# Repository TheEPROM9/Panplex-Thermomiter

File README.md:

# Panplex-Thermomiter
Website Overview: https://www.theeprom9.co.uk/electronics/projects-such/panplex-thermometer
Here be the PCB files & code I developed for this project.

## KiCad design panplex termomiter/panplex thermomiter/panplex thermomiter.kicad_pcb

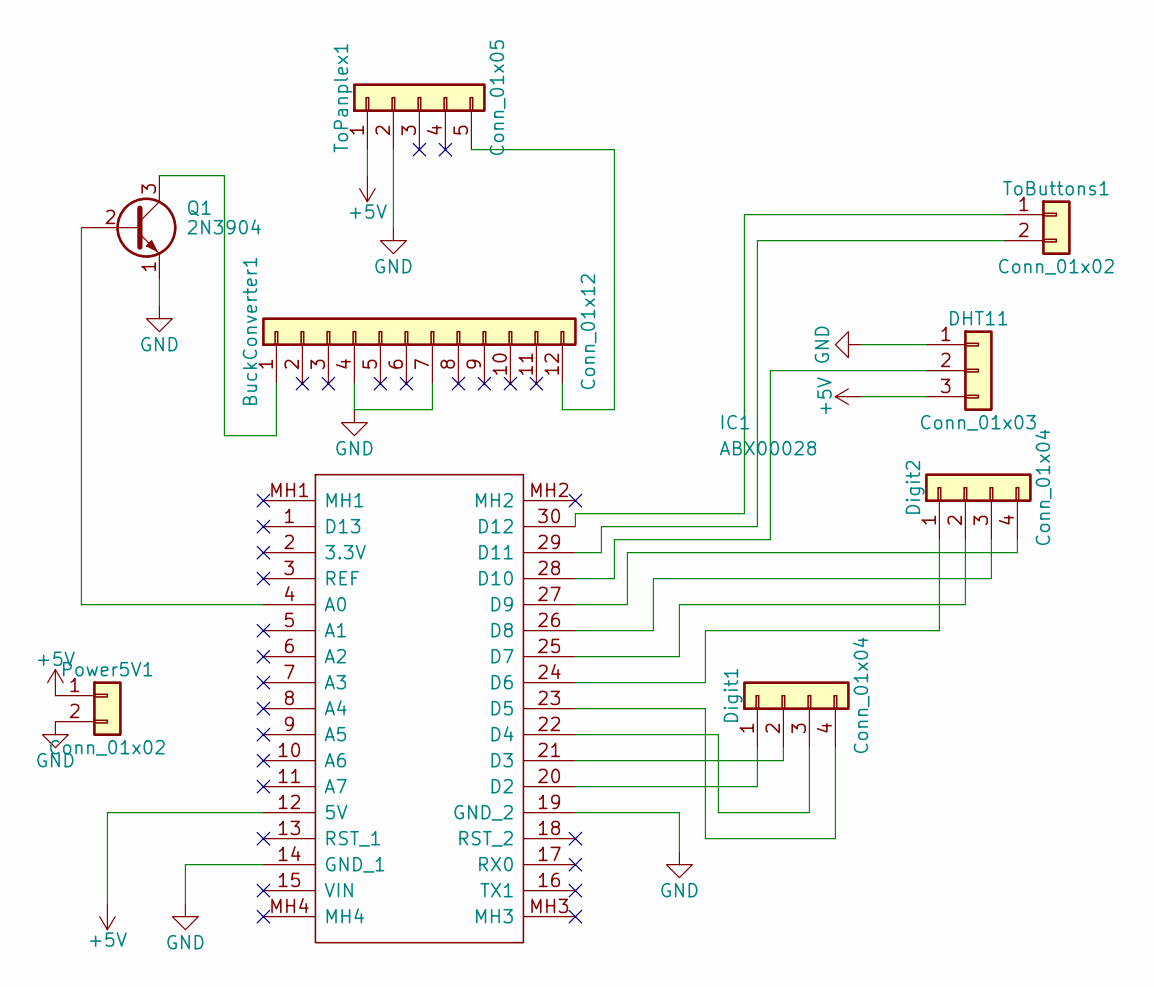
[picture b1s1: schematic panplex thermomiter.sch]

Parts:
BuckConverter1: Conn_01x12; nixi-serply-custom
DHT11: Conn_01x03; Pin_Header_Angled_1x03_Pitch2.54mm
Digit1, Digit2: Conn_01x04; Pin_Header_Angled_1x04_Pitch2.54mm
IC1: ABX00028; Arduino_Nano; Manufacturer_Part_Number ABX00028; Mouser Part Number 782-ABX00028
Power5V1: Conn_01x02; Pin_Header_Angled_1x02_Pitch2.54mm
Q1: 2N3904; TO-92_Molded_Narrow
ToButtons1: Conn_01x02; Pin_Header_Angled_1x02_Pitch2.54mm
ToPanplex1: Conn_01x05; Pin_Header_Angled_1x05_Pitch2.54mm

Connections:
+5V: DHT11.3, IC1.12 (5V), Power5V1.1, ToPanplex1.1
GND: BuckConverter1.4, BuckConverter1.7, DHT11.1, IC1.14 (GND_1), IC1.19 (GND_2), Power5V1.2, Q1.1 (E), ToPanplex1.2
unnamed: BuckConverter1.1, Q1.3 (C)
unnamed: BuckConverter1.12, ToPanplex1.5
unnamed: DHT11.2, IC1.28 (D10)
unnamed: Digit1.1, IC1.20 (D2)
unnamed: Digit1.2, IC1.21 (D3)
unnamed: Digit1.3, IC1.22 (D4)
unnamed: Digit1.4, IC1.23 (D5)
unnamed: Digit2.1, IC1.24 (D6)
unnamed: Digit2.2, IC1.25 (D7)
unnamed: Digit2.3, IC1.26 (D8)
unnamed: Digit2.4, IC1.27 (D9)
unnamed: IC1.4 (A0), Q1.2 (B)
unnamed: IC1.29 (D11), ToButtons1.2
unnamed: IC1.30 (D12), ToButtons1.1

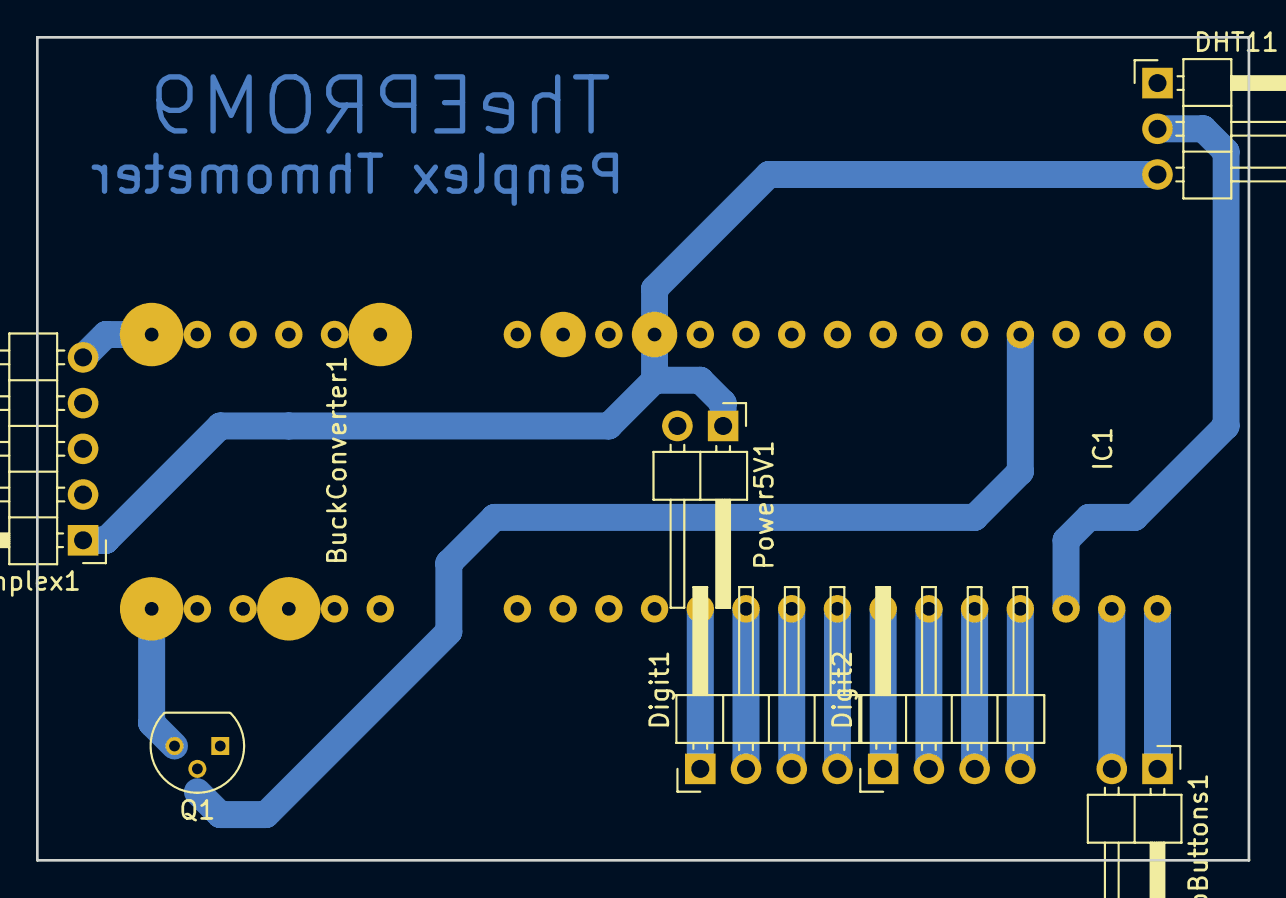
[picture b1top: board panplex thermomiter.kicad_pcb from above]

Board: 2 copper layers, 67.3 x 45.7 mm, 9 parts (0 on the bottom side), 16 nets.
